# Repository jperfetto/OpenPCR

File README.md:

# OpenPCR
Software for the OpenPCR thermocycler

## Organization
- air - Adobe AIR-based user interface
- arduino/openpcr - the core real-time control application for the OpenPCR
- ncc - "No Cache Cat" utility program utilized by the Adobe AIR application to read mass USB filesystem without caching
- usb - software to make the Arduino's USB chip act as a mass storage device, to facilitate communications with the Adobe AIR application

## For more information
- Visit [openpcr.org](http://openpcr.org) for more information on the OpenPCR project
- Visit [www.chaibio.com/openpcr](https://www.chaibio.com/openpcr) to purchase an OpenPCR device

## License
OpenPCR is licensed under [GNU GPLv3](http://www.gnu.org/copyleft/gpl.html).

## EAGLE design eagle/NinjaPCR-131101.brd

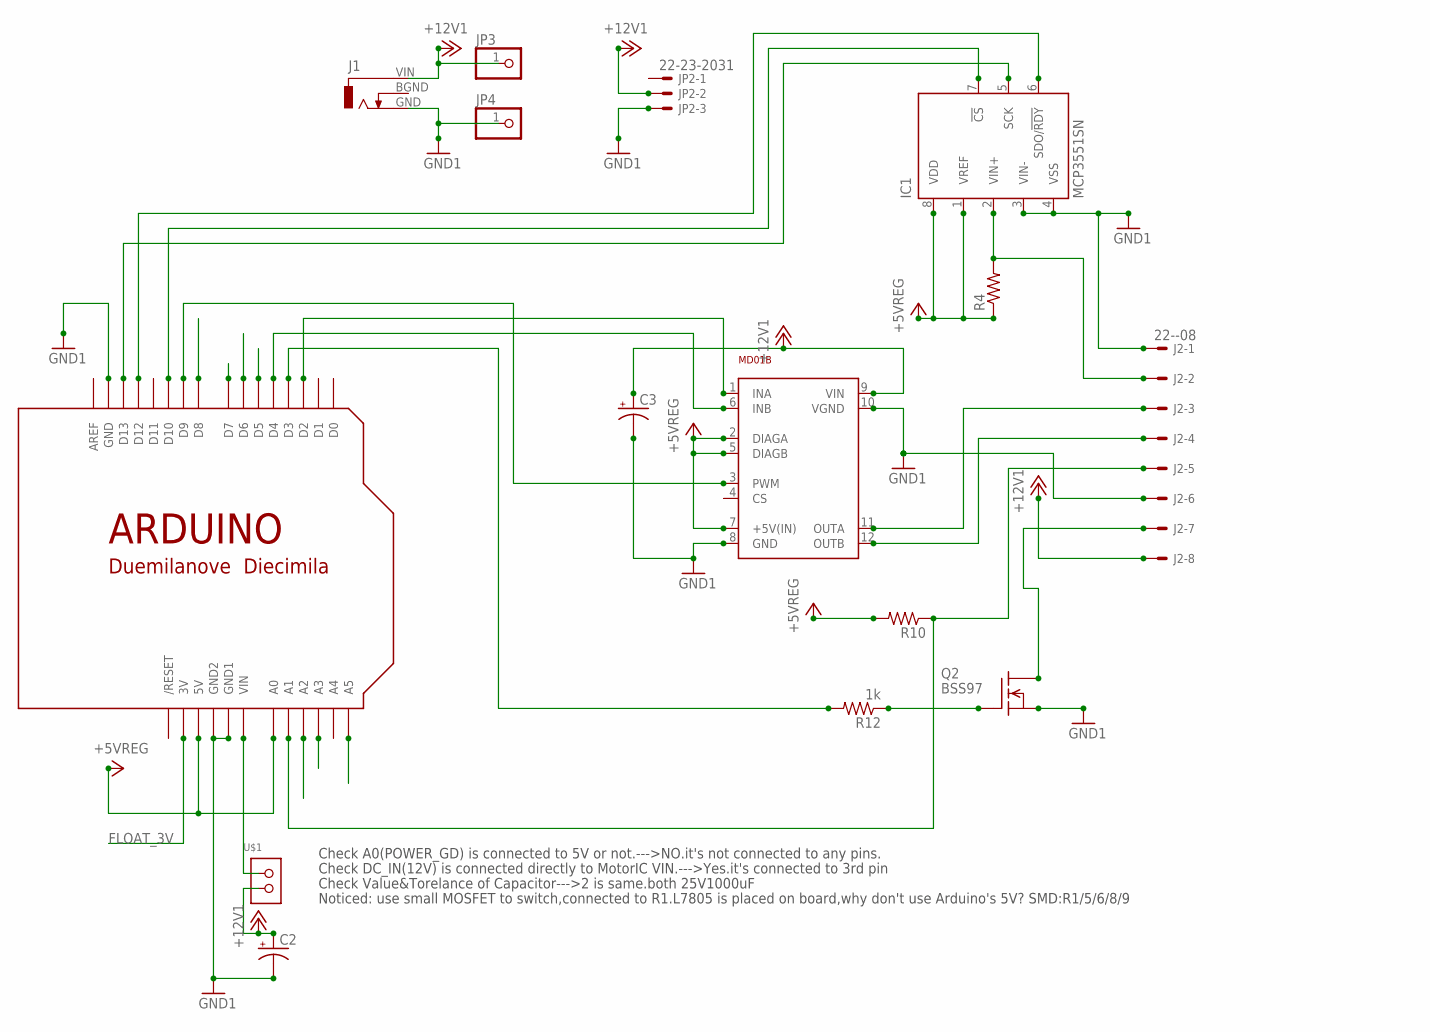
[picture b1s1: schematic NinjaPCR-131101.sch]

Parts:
C2: CPOL-USE5-8.5; E5-8,5
C3: CPOL-USE5-13; E5-13
IC1: MCP3551SN; SO-08
J1: DCJ0303
J2: 22--08; POLOLU-8-VERTICAL
JP2: 22-23-2031
JP3, JP4: PINHD-1X1; 1X01
MD01B: VNH3SP30+4PINN; VNH3SP30+4PIN_NOHOLES
Q2: BSS97; TO202
R4, R10: R-US_0207/10; 0207/10
R12: 1k; 0207/10
U$1: 1X02; 1X02_1.1_UNSIGNED
U$3: ARDUINODUEMILANOVE; ARDUINO

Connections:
+5VREG: IC1.1 (VREF), IC1.8 (VDD), MD01B.2 (DIAGA), MD01B.5 (DIAGB), MD01B.7 (+5V(IN)), R4.1, R10.2, U$3.5V, U$3.A0
+12V1: C2.+, C3.+, J1.VIN, J2.8, JP2.2, JP3.1, MD01B.9 (VIN), U$1.2
D13: IC1.5 (SCK), U$3.D13
FLOAT_3V: U$3.3V
GND1: C2.-, C3.-, IC1.3 (VIN-), IC1.4 (VSS), J1.GND, J2.1, J2.6, JP2.3, JP4.1, MD01B.8 (GND), MD01B.10 (VGND), Q2.1 (S), U$3.GND, U$3.GND1, U$3.GND2
unnamed: U$1.1, U$3.VIN
unnamed: R12.2, U$3.D3
unnamed: J2.3, MD01B.11 (OUTA)
unnamed: J2.4, MD01B.12 (OUTB)
unnamed: J2.7, Q2.2 (D)
unnamed: IC1.2 (VIN+), J2.2, R4.2
unnamed: IC1.6 (SDO/!RDY), U$3.D12
unnamed: IC1.7 (!CS), U$3.D10
unnamed: J2.5, R10.1, U$3.A1
S$1: MD01B.1 (INA), U$3.D2
S$2: MD01B.3 (PWM), U$3.D9
S$3: MD01B.6 (INB), U$3.D4
T1: Q2.3 (G), R12.1

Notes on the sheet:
Check A0(POWER_GD) is connected to 5V or not.--->NO.it's not connected to any pins.
Check DC_IN(12V) is connected directly to MotorIC VIN.--->Yes.it's connected to 3rd pin
Check Value&Torelance of Capacitor--->2 is same.both 25V1000uF
Noticed: use small MOSFET to switch,connected to R1.L7805 is placed on board,why don't use Arduino's 5V? SMD:R1/5/6/8/9

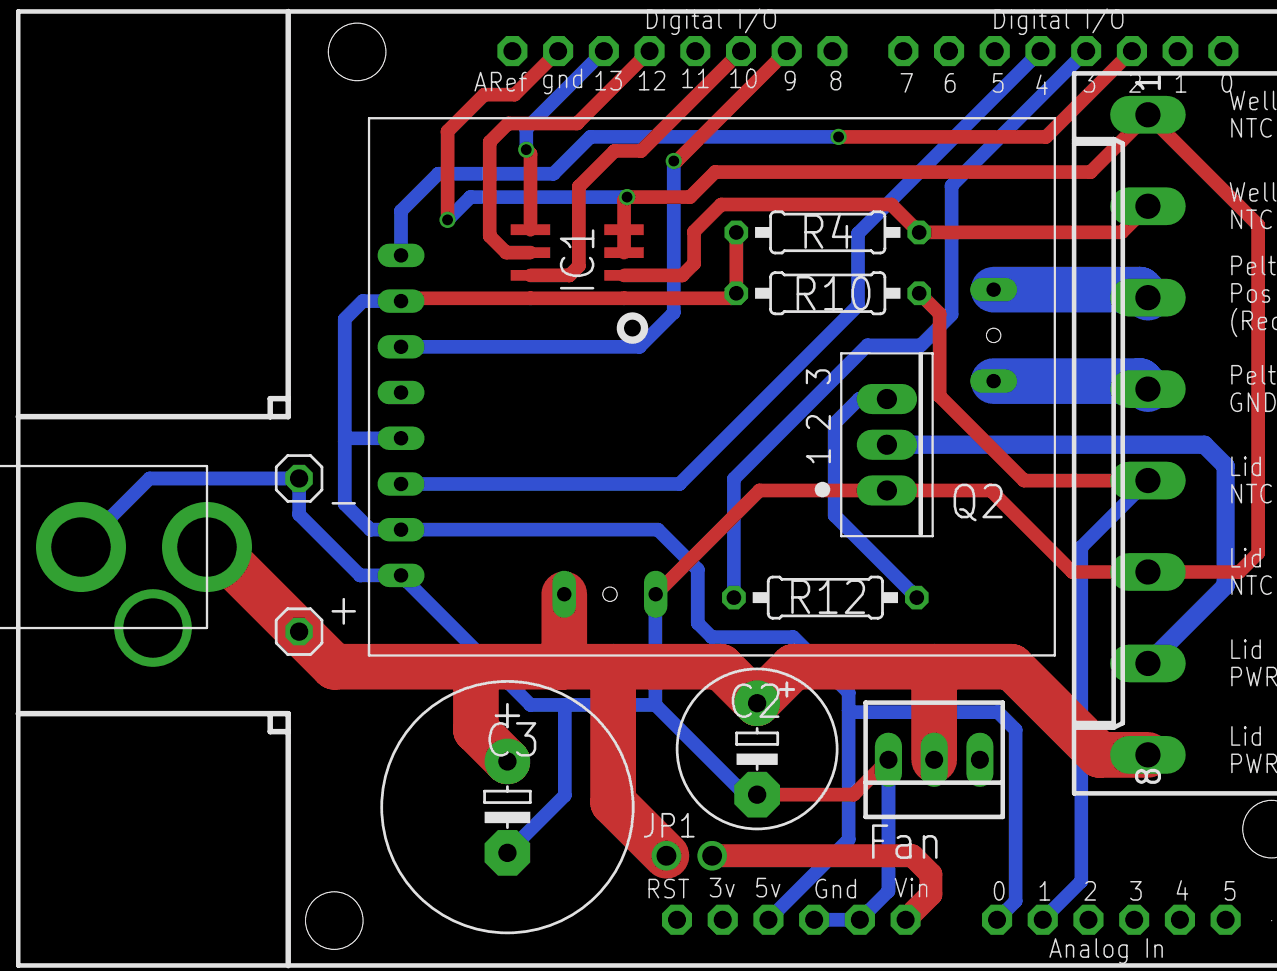
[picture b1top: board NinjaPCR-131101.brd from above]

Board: 2 copper layers, 15 parts (0 on the bottom side), 17 nets.

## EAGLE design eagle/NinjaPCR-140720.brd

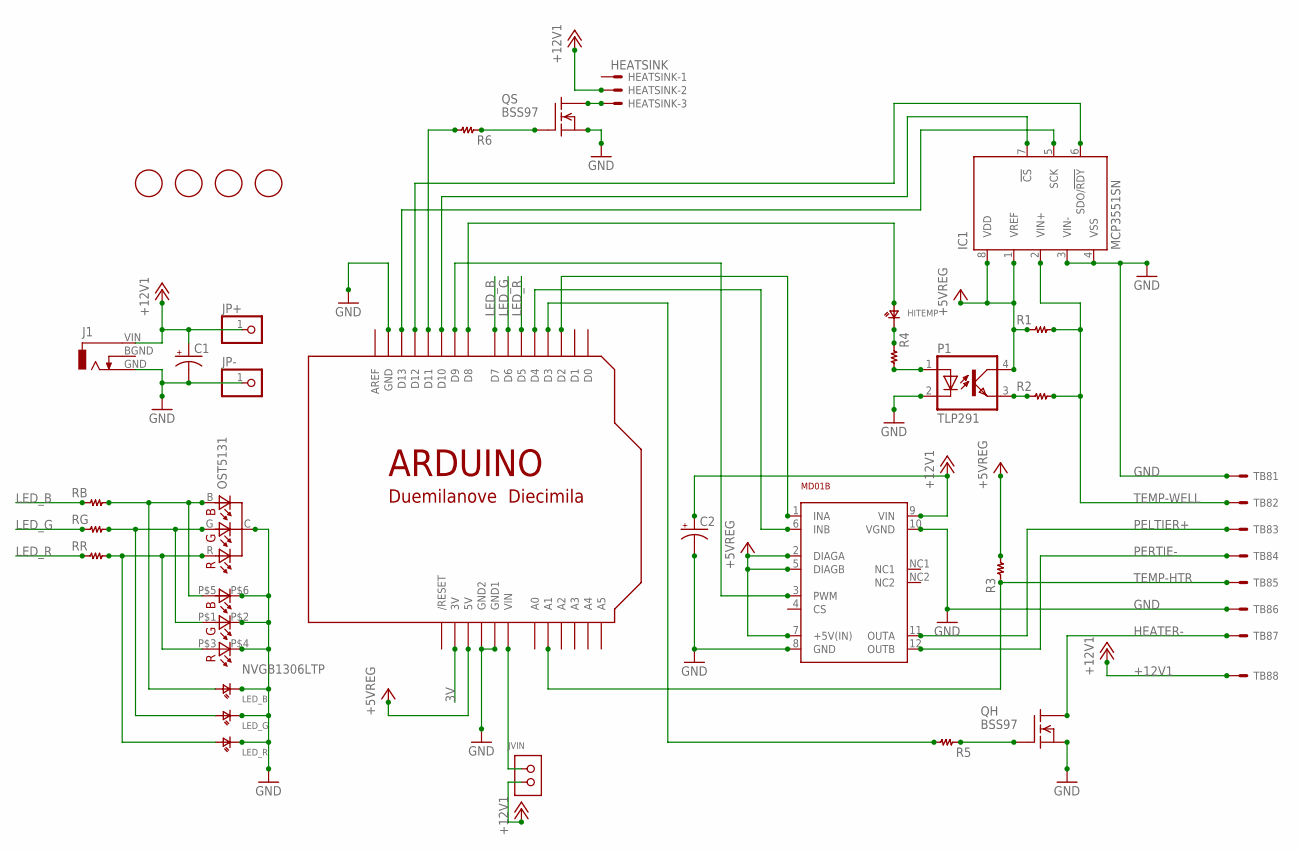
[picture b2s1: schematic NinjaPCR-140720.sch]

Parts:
C1: CPOL-USE5-8.5; E5-8,5
C2: CPOL-USE5-13; E5-13
HEATSINK: HEATSINK; 22-23-2031
HITEMP: LED1608; SMD_1608_0603
IC1: MCP3551SN; SO-08
J1: DCJ0303
JP+: PINHD-1X1; 1X01
JP-: PINHD-1X1; 1X01
JVIN: 1X02; 1X02_1.1_UNSIGNED
LED_B: LED2012; SMD_2012_0805
LED_G: LED2012; SMD_2012_0805
LED_R: LED2012; SMD_2012_0805
MD01B: VNH3SP30+4PINN; VNH3SP30+4PIN_NOHOLES
P1: TLP291; MINI-FLAT-4
QH: BSS97; TO202
QS: BSS97; TO202
R1, R2, R3, R4, R5, R6: R_SMD1608; SMD_1608_0603
RB: R_SMD1608; SMD_1608_0603
RG: R_SMD1608; SMD_1608_0603
RR: R_SMD1608; SMD_1608_0603
TB8: TB112A-2-8
U$1: OST5131; OSTA5131
U$2, U$4, U$5, U$6: FIDUCIAL; FIDUCIAL_1MM
U$3: ARDUINODUEMILANOVE; ARDUINO
U$8: NVGB1306LTP; NVGB1306L_TINYPADS

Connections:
3V: U$3.3V
+5VREG: IC1.1 (VREF), IC1.8 (VDD), MD01B.2 (DIAGA), MD01B.5 (DIAGB), MD01B.7 (+5V(IN)), P1.4 (COL), R1.P$1 (1), R3.P$2 (2), U$3.5V
+12V1: C1.+, C2.+, HEATSINK.2, J1.VIN, JP+.1, JVIN.2, MD01B.9 (VIN), TB8.P$8
B: LED_B.P$1 (A), RB.P$2 (2), U$1.B (BA), U$8.P$5 (BA)
D13: IC1.5 (SCK), U$3.D13
G: LED_G.P$1 (A), RG.P$2 (2), U$1.G (GA), U$8.P$1 (GA)
GND: C1.-, C2.-, IC1.3 (VIN-), IC1.4 (VSS), J1.GND, JP-.1, LED_B.P$2 (C), LED_G.P$2 (C), LED_R.P$2 (C), MD01B.8 (GND), MD01B.10 (VGND), P1.2 (C), QH.1 (S), QS.1 (S), TB8.P$1, TB8.P$6, U$1.C (CC), U$3.GND, U$3.GND1, U$3.GND2, U$8.P$2 (GC), U$8.P$4 (RC), U$8.P$6 (BC)
HEATER-: QH.2 (D), TB8.P$7
LED_B: RB.P$1 (1), U$3.D7
LED_G: RG.P$1 (1), U$3.D6
LED_R: RR.P$1 (1), U$3.D5
unnamed: HEATSINK.3, QS.2 (D)
unnamed: QS.3 (G), R6.P$1 (1)
unnamed: R6.P$2 (2), U$3.D11
unnamed: P1.3 (EMIT), R2.P$1 (1)
unnamed: JVIN.1, U$3.VIN
unnamed: HITEMP.P$1 (A), U$3.D8
unnamed: P1.1 (A), R4.P$2 (2)
unnamed: R5.P$2 (2), U$3.D3
unnamed: HITEMP.P$2 (C), R4.P$1 (1)
unnamed: IC1.6 (SDO/!RDY), U$3.D12
unnamed: IC1.7 (!CS), U$3.D10
NC1: MD01B.NC1
NC2: MD01B.NC2
PELTIER+: MD01B.11 (OUTA), TB8.P$3
PERTIE-: MD01B.12 (OUTB), TB8.P$4
R: LED_R.P$1 (A), RR.P$2 (2), U$1.R (RA), U$8.P$3 (RA)
S$1: MD01B.1 (INA), U$3.D2
S$2: MD01B.3 (PWM), U$3.D9
S$3: MD01B.6 (INB), U$3.D4
T1: QH.3 (G), R5.P$1 (1)
TEMP-HTR: R3.P$1 (1), TB8.P$5, U$3.A1
TEMP-WELL: IC1.2 (VIN+), R1.P$2 (2), R2.P$2 (2), TB8.P$2

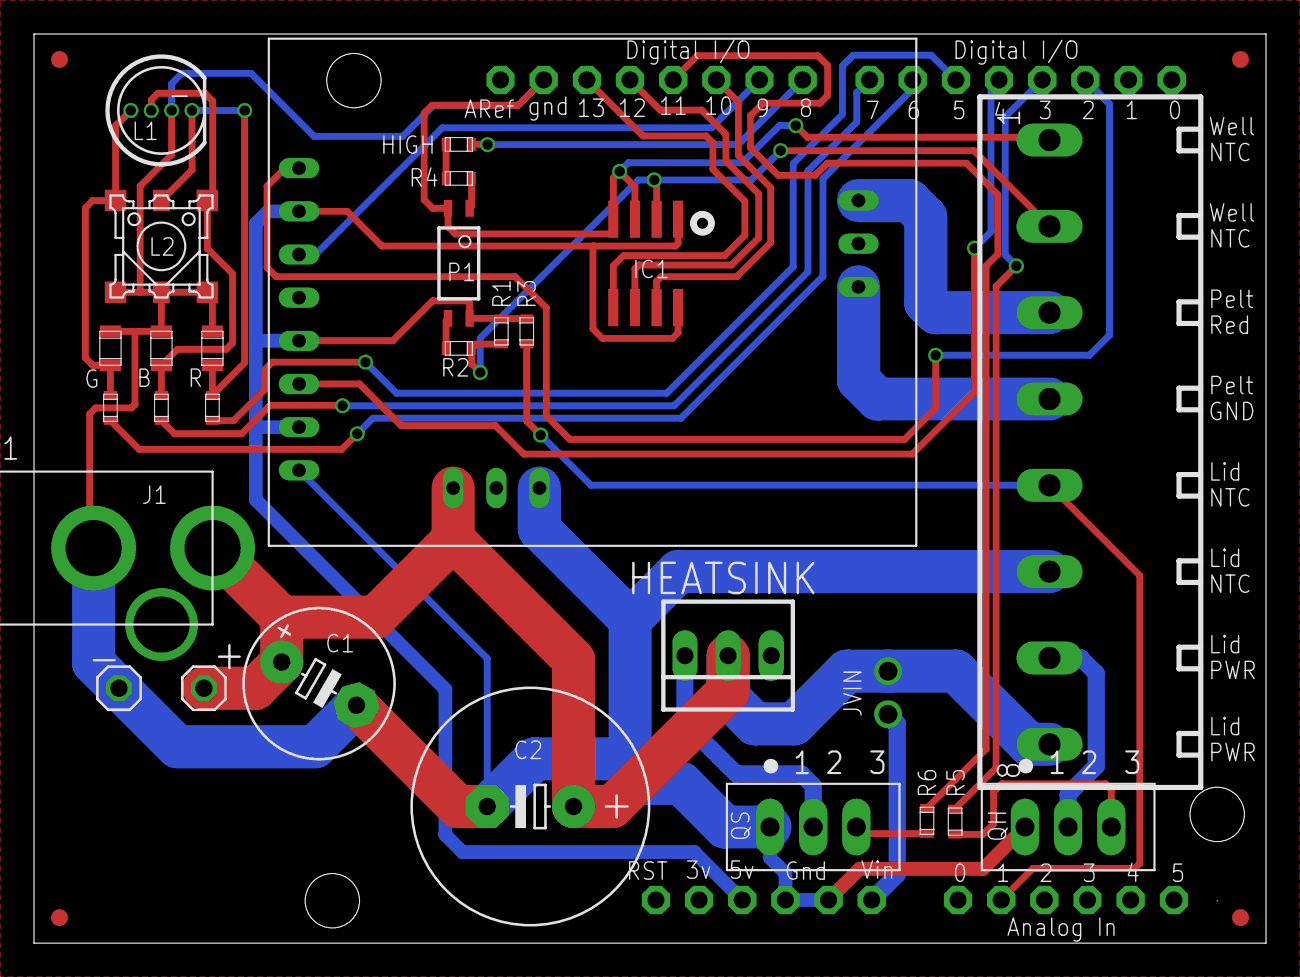
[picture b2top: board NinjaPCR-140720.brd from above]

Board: 2 copper layers, 72.5 x 53.5 mm, 33 parts (0 on the bottom side), 30 nets.

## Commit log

2010-03-27 Initial Revision
2010-03-27 Add contents this time
2010-03-29 Add basic temp regulation
2010-05-11 Integrate with ADC over SPI for more accurate temperature measurements
2010-05-22 Machine is now cycling
2010-10-20 Changes for heated lid control
2010-11-18 Add GPLv3 License
2010-11-18 Add copyright notice
2010-11-18 Remove foobar from license
2010-11-18 Add license file
2010-12-11 Updates for new circuitry
2011-02-11 Remove serial proxy
2011-02-11 Move arduino code to subdir
2011-02-11 Remove test air code
2011-03-02 Minor changes while debugging
2011-03-02 Re-arrange directory structure for Arduino sketch util
2011-03-02 Remove debugging code
2011-03-08 Add initial mass storage example
2011-03-09 Latest debugging code
2011-04-24 Round decimals properly in LCD display
2011-04-24 Add Arduino PID library
2011-04-24 Switch to new PID library for block + lid, initial PID tuning
2011-04-24 Remove legacy PID code
2011-04-24 Fix floating point rounding
2011-04-29 Improve PID algorithm
2011-04-29 Reset display every mintue
2011-04-29 Add bang-bang control for lid heater
2011-04-29 Add ETA algorithm
2011-04-30 Make a dummy commit
2011-04-30 First version of OpenPCR App
2011-04-30 Tweak ETA algorithm
2011-04-30 Add git ignore for AVR Studio files
2011-04-30 Setup USB software in AVR Studio
2011-05-27 Fix bug with display of ETAs ending in 0 minutes
2011-06-05 Fix display of negative temp values
2011-06-06 FAT16 File System working
2011-06-08 Add debug display capability for debugging
2011-06-08 Update serial protocol for new length definition
2011-06-08 USB serial comms working
2011-06-08 Add Win32 no cache cat
2011-06-10 Status and Stop serial commands working
2011-06-10 2-way serial commands working
2011-06-10 Add .s files to gitignore
2011-06-10 Update ncc workspace
2011-06-10 Updated to work with USB interface
2011-06-10 Change from smoothness to redmond theme
2011-06-13 Add makefile to build with listing files
2011-06-13 Implement dynamic programming, fix numerous bugs
2011-06-13 Send 256 bytes to arduino
2011-06-13 workspace changes
2011-06-20 Updating USB connectivity to AIR
2011-06-22 Wait for lid to heat before starting PCR run
2011-06-22 Refactor run completion code
2011-06-22 Fix bug with temp instability when 2 concurrent steps have same temp, refactor thermal state display code
2011-06-22 Fix bug with display of final step program name
2011-06-22 Remove hard-coded program
2011-06-22 Initialize program name so we don't print garbage
2011-06-24 Use pools for steps/cycles
2011-06-24 Fix display corruption after program with no final step
2011-06-24 Improve read performance for status.txt so as to not delay PID calculations, remove erroneous values from status.txt when machine is stopped
2011-06-24 Air app status will update while lid is heating to temp
2011-06-25 Air UI continues to update after protocol is completed
2011-06-25 Reading from the running file is now started/stopped when a protocol is started/stopped. Caused a bug where OpenPCR was read from multiple times per cycle
2011-06-25 Formatting changes and version # changes
2011-06-25 Add optimized PID tuning for lower temps
2011-06-25 Remove unneeded I2C params
2011-06-25 Refactor command parser out of SerialControl
2011-06-25 Revise copyright notices
2011-06-25 Restart last program on power-on, don't restart if we detected a previous crash
2011-06-25 Fix bug with 1-repeate cycles
2011-06-25 Added code to update command ID after stop
2011-06-25 Status file is read every second once app is started. Used to wait for Start to be sent
2011-06-25 Updated so protocol sent to device is maximum of 3 elements at top level
2011-06-25 Move all strings into PROGMEM to conserve SRAM
2011-06-25 Don't auto-start if status.txt is read
2011-06-25 Remove erroneously committed build dir
2011-06-26 Fix bug with not auto-starting when connected to air app
2011-06-26 Misc stuff
2011-06-26 Improve PID performance for decreasing at high temps
2011-06-26 Other misc changes
2011-06-26 Optimize PID control at low increasing temps, decrease max steps to 25 to free memory
2011-06-26 Add autorun.inf to disable auto-open of explorer on WinXP/Vista, does not work on Win 7
2011-06-26 Improve crash/restart detection, works more reliably and auto-run now works on fast power cycles
2011-06-27 Improve restart detection algorithm
2011-06-27 Tweak initial ETA calculations to assume 1 C/s ramp times
2011-06-27 Fixed USB volumechangeevents in Windows by instead tracking drive name rather than the real path
2011-06-29 Free up memory by using 20 max cycles, moving sprintfloat form strings to progmem
2011-06-29 Make auto-start more robust against inconsistent initial memory
2011-07-09 Version 1.0 package. Updated NativeApplicationUpdater to download software updates
2011-08-08 Add OSX NCC
2011-08-08 Add Linux NCC
2011-12-17 Fix cycle count display when having an initial step
2011-12-18 Rev version number
2012-01-14 Add config command for contrast adjustment
2012-01-14 Offical 1.0.2 release, fixed contrast bug when program starts
2012-04-29 Rename OpenPCR folder
2012-04-29 Upgraded project to work with new Arduino IDE
2012-05-23 OpenPCR 1.0.3
2012-05-23 Update air software to 1.0.1 to support contrast setting
2012-05-23 Add ncc workspace
2012-06-10 Fix a simple test default experiment, remove other experiments, rev version to 1.0.2
2012-06-18 Begin implementing ramp duration control, refactor thermistor.cpp a bunch to simplify
2012-06-18 minor refactor
2012-06-18 Basic delayed ramp control in place
2012-06-20 Controlled ramp now working, needs tuning
2012-06-20 Enable controlled ramp in AIR UI, needs backwards compatability
2012-06-30 Implement new PID alg w/ gain scheduling and different anti-windup, lid uses new PID alg, increase thermistor read rate by eliminating serial blocking
2012-10-10 ETA accurate for slow ramps
2012-10-19 Fix bug with buffer overrun resulting from slow ramp changes
2012-10-19 Reduce step name length by 2 bytes as display does not have room for those bytes anyways
2013-06-19 add test.txt
2013-06-19 remove test.txt
2013-06-19 Add Arduino Source Files
2013-06-19 Prepare message files for i18n
2013-06-19 Localize app name & app description
2013-06-19 Add README.md
2013-06-19 Hide debug button
2013-06-19 Adjust margin of device list
2013-06-19 Check firmware version and show dialog if latest version is available
2013-06-19 Plug & Play
2013-06-20 Enable "About" dialog
2013-06-20 Remove useless scripts
2013-06-20 Add i18n library (from my repository https://github.com/maripo/CustomFilter)
2013-06-20 Fix margin size of buttons
2013-06-20 Remove useless HTML
2013-06-20 Initialize i18n lib
2013-06-20 Remove useless include
2013-06-20 Remove unused codes
2013-06-20 Remove unused code
2013-06-20 Read & add step names
2013-06-20 Close serial connection before shutdown
2013-06-20 Localize messages in HTML
2013-06-20 Localize step names
2013-06-20 Japanese translation
2013-06-20 Localize graph
2013-06-21 Change styles
2013-06-26 renamed
2013-06-27 add reference url
2013-06-27 Post Receive Test
2013-06-27 Push Receive Test
2013-06-27 upload 2d/3d parts
2013-06-27 add 3d models
2013-06-27 add readme
2013-06-27 update name of Knob from M12 to M6
2013-06-27 update url
2013-06-28 rename to NinjaPCR
2013-07-05 add stl&igs data
2013-07-15 change thermistor parameter on well
2013-07-16 remove random kill
2013-07-17 tune R const on well
2013-07-17 debug resistance
2013-07-17 oops
2013-07-17 update resistance param to unsigned long
2013-07-19 add thermal bath parameter
2013-07-21 Support Leonardo
2013-07-21 remove resistance sysout
2013-07-23 Support UNO
2013-07-23 UNOテスト用 / Leonardo対応による不具合を修正
2013-07-24 Switch by TCCR2A instead of "LEONARDO"
2013-07-24 Abandon LEONARDO
2013-07-24 Add leveled logging system (Log.e, Log.w, Log.i, Log.d, Log.v)
2013-07-24 reduce Y length of the window
2013-07-25 Check serial connection timeout
2013-07-26 Preparation for "re-start" feature
2013-07-28 Chage debug level
2013-07-28 No.3 thermal parameter added
2013-07-28 Fix a bug (Initial "pcrX.X.X" messages were sent too frequently)
2013-07-29 Add variations of scales to the graph (10sec - 8h)
2013-07-29 Stop serial communication - after experiments - after "stop" commands from Chrome app
2013-07-29 Change "download" tag (input->anchor)
2013-07-29 Add "timeout" feature (Continue thermo-cycler without receiving serial message from Chrome app)
2013-07-29 * Add debug messages * Change debug level of "Connection Lost" message (debug->warning)
2013-07-29 Add a validation rule to "Final Hold" (The value should be 16C or more)
2013-07-29 Show "Home" button, stop serial communication and clear the graph after experiments
2013-07-31 clean cad files
2013-07-31 add latest eagle files
2013-07-31 温度パラメタを更新
2013-08-02 Sefial Timeout (avoid continuous cooling & heating after disconnection)
2013-08-02 Fix bug: Could not download a CSV file after executing a new experiment
2013-08-02 Add a version
2013-08-02 Add build script for NinjaPCR & Makers Toy PCR * Replace "NinjaPCR" with "Makers Toy PCR" for Makers Toy PCR * Ignore generated directories and archive files
2013-08-03 Fix style of #OpenDownloadPage
2013-08-03 Add gradient texture to "A" tag buttons
2013-08-05 Change class of the "Unplugged" alert dialog to avoid conflict with the "Start" button
2013-08-05 Refactor (Change an ambiguous method name)
2013-08-05 Set visibility of the "Unplugged" dialog right after a device is found.
2013-08-06 add photos
2013-08-06 add more photos
2013-08-07 Display elapsed time
2013-08-07 Remove useless println
2013-08-07 Alert serial timeout
2013-10-07 add vertical coolers because it's cheaper!
2013-10-07 export sat/step/stl formats to test whether it's possible to design both in Mac and Win
2013-10-07 add Vertical Cooler to save money
2013-10-09 adding DeepCooler
2013-10-14 add facebook album url
2013-10-14 remove photos.refer facebook album at https://www.facebook.com/hisakawa/media_set?set=a.10151895843079481.663784480&type=3
2013-10-14 it's GPL!
2013-10-14 add logo
2013-11-02 shrinking and shrinking
2013-11-02 directory moving
2013-11-02 Not yet decided how to cover sides of top lid with acryl.
2013-11-06 ready to cut
2013-11-14 update to cut
2014-02-03 add photo
2014-02-03 change photo
2014-07-26 moving to fusion360
2014-07-26 moving to fusion 360
2014-07-26 move to fusion 360
2014-08-11 Remove and ignore Thums.db
2014-08-11 Support new serial API in initial scanning process
2014-08-11 Replace obsolete "getPorts" with "getDevices" method
2014-08-11 Rename "Save" function (to follor the coding rule)
2014-08-11 Solve Issue #105 (Call a callback funcrion in "save")
2014-08-12 Switch thermistor configuration with preprocessor definition
2014-08-12 Add ohm-celcius table for the new thermistor (NXFT15WF104FA2B100)
2014-08-12 Add resistor switching logic
2014-08-14 Get rid of "chrome.serial.read" and add wrapper of chrome.serial.onReceive
2014-08-15 Add debug code
2014-08-18 * Support resistor switching feature * Fix plate resistance table
2014-11-15 Misc.
2014-11-15 Separate varied thermistor tables into thermistor_table.h
2014-12-01 Add thermistor table generator
2014-12-01 Add thermistor management code
2014-12-01 Fix bug in port scanning logic
2014-12-01 Add ignore condition (port scanning)
2015-08-04 add pcbs
